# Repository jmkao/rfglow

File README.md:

rfglow
======

All the parts for an RF controlled RGB glow stick, in the style of a Ruifan KING BLADE (キングブレード http://ruifan.co.jp/pro_kb_x.html). In fact, making this work requires a diffuser from a KB since the diffuser itself cannot be 3D printed.

There are 3 basic component areas:
 * Electronics (Eagle files and BOM)
 * Microcontroller code (Arduino code)
 * Plastic handle (Inventor IPT files and STL files for 3D printing)

## Project Chat

## Status
This project is fairly usable, although could use some additional polish. All of the areas are sufficiently functional to demonstrate a proof of concept, but requires more testing before a device could actually be used in a physically demanding environment.

The primary items that need work are:
 * App for the BLE master
 * Handle design - Refactor to be more compact and with more practical design, especially for the coupler and attachemnt of the two halves
 * RF Master - Integrate a 0.96" color OLED screen, then design a PCB for it
 * RF Slave - Code something for the button to do

Then there are other interesting things that one could do with a microcontroller:
 * Fade commands
 * Color cycling commands
 * Slaves also act as command repeaters

Contributions welcome in all areas.

# Electronics
The PCB design is in the eagle folder and contains the schematic, PCB layout, and a set of gerber files (zipped together) for sending to a PCB fabrication service like Osh Park or Seeedstudio. (I had my first set made at Osh Park.)

The PCB is really a kind of motherboard for a variety of sub-assemblies (other boards sold as modules), principally:
 * RFBee from Seeedstudio
  * A Panstamp from panstamp.com can also be used as it has the same hardware (and is more compact, even). However, I don't have  board design to accomodate one (yet!)
 * Pololu S7V8A Adjustable Regulator (http://www.pololu.com/product/2118)
  * The potentiometer on this should be adjusted to output 3.7V before putting in place on the board
 * STP04CM05 LED Driver
  * The one I used for this design is a 14-DIP package not officially mentioned on the datasheet. I got mine from Digi-key (http://www.digikey.com/product-detail/en/STP04CM05B1R/497-6940-5-ND/1852497).
 * Vollong 3W RGB High Power Led and a matching lens
  * I got mine from http://www.superbrightleds.com/moreinfo/component-leds/vollong-3w-rgb-high-power-led/899/2214/
  * You'll need to bridge together the - leads into a common cathode configuration (the STP04CM05 is a sink driver)
 * Grove connectors from Seeedstudio cut up
  * I'm sure there's some spec for these, but I had a bunch of these lying around and used them for this purpose. Since you'll have to order an RFBee from them, you might as well get a bunch of cables from them (male on both sides so each cable can make two connectors) and PCB receptacles.
  * The color convention I'm using is:
    * Cable Red --> LED Red
    * Cable White --> LED Green
    * Cable Yellow --> LED Blue
    * Cable Black --> LED Common Ground
 * Adafruit nRF8001 (https://www.adafruit.com/products/1697)
  * Used for the rfglow_ble code which will relay commands from the nRF8001's BLE interface to the glow sticks.
  * Would allow a mobile app (e.g. iOS, Android) on a BLE capable device to control the glow sticks with a more advanced interface
  * A panstamp must be used as the microcontroller to build this device because the nRF8001 must be wired to the hardware SPI interface, and the RFBee does not expose the pins necessary to do this.

The version of the BLE master in this repository is for an unamplified version that uses a Panstamp. There is also an amplified designed that uses a CC1101+CC1190 evaluation module. The schematics and board layout for that were done in Upverter and are available at https://upverter.com/jkao/e86d81299623de9d/RFGlow-BLE-CC1109-Relay/

# Microcontroller Code

Arudino Code for 1.0.x.

 * rfglow_slave
  * Code for the glow sticks themselves
 * rfglow_master
  * Code for a potential master
  * Currently supported gestures:
   * Color change - short press on left and right
   * LED on/off - long press on the center to toggle
   * Auto color cycling mode - short press on center to toggle
   * Brightness change - long press on left or right
 * rfglow_ble
  * BLE based master that will relay color change commands over BLE to the RF glow sticks
  * Usable today for simple color changes with the iOS nRF UART or LightBlue apps
   * For nRF UART, send ASCII of 3 numbers separated by spaces, like "270 255 32\n". This is an HSV value, with the first digit as hue (0-359), second digit as saturation (0-255), and third digit as brightness (0-255)
   * For LightBlue (and really for any app you design yourself), send 4 bytes to the write characteristic of the service. The first 2 bytes are a 16-bit unsigned int for hue (only valid from 0-355), the 3rd byte is the unsigned 8-bit int for saturation, the 4th byte is the unsigned 8-bit int for brightness.
 * rfglow_serial
  * Code for when the master is connected to a computer, in which case you can enter the hue, saturation, and brightness as tuples over the serial line to send the command.
  * This code hasn't been touched in a while, and needs to have the radio settings from rfglow_master copied into it for it to actually work with the current version of rfglow_slave

The Arduino code depends on the following libraries:
 * ShiftPWM from https://github.com/elcojacobs/ShiftPWM
 * Panstamp for Arudino 1.0.x, currently panstamp_library.zip from http://www.panstamp.com/downloads
  * Uses only the CC1101 libraries and not the SWAP stack
 * ClickButton from https://code.google.com/p/clickbutton/downloads/list
  * Only needed by rfglow_master currently for the button behavior

# Plastic Handle

Autodesk Inventor parts and assembly with the current design, to be FFF 3D printed (e.g. <45 degree overhangs, etc...).

This design is quite messy becuase my CAD skills are weak, and the parameters are difficult to adjust. However, it is functional with the following features:
* Lip-and-groove attachment between top and bottom halves to facilitate alignment
 * There is some clearance, so the groove is deeper than the lip sticks out
* Coupler to screw on a king blade diffuser on one end, then attach to the handle
* Cups for magnets to help hold the top and bottom together (0.25" X 0.125" X 0.0625" rare earth)

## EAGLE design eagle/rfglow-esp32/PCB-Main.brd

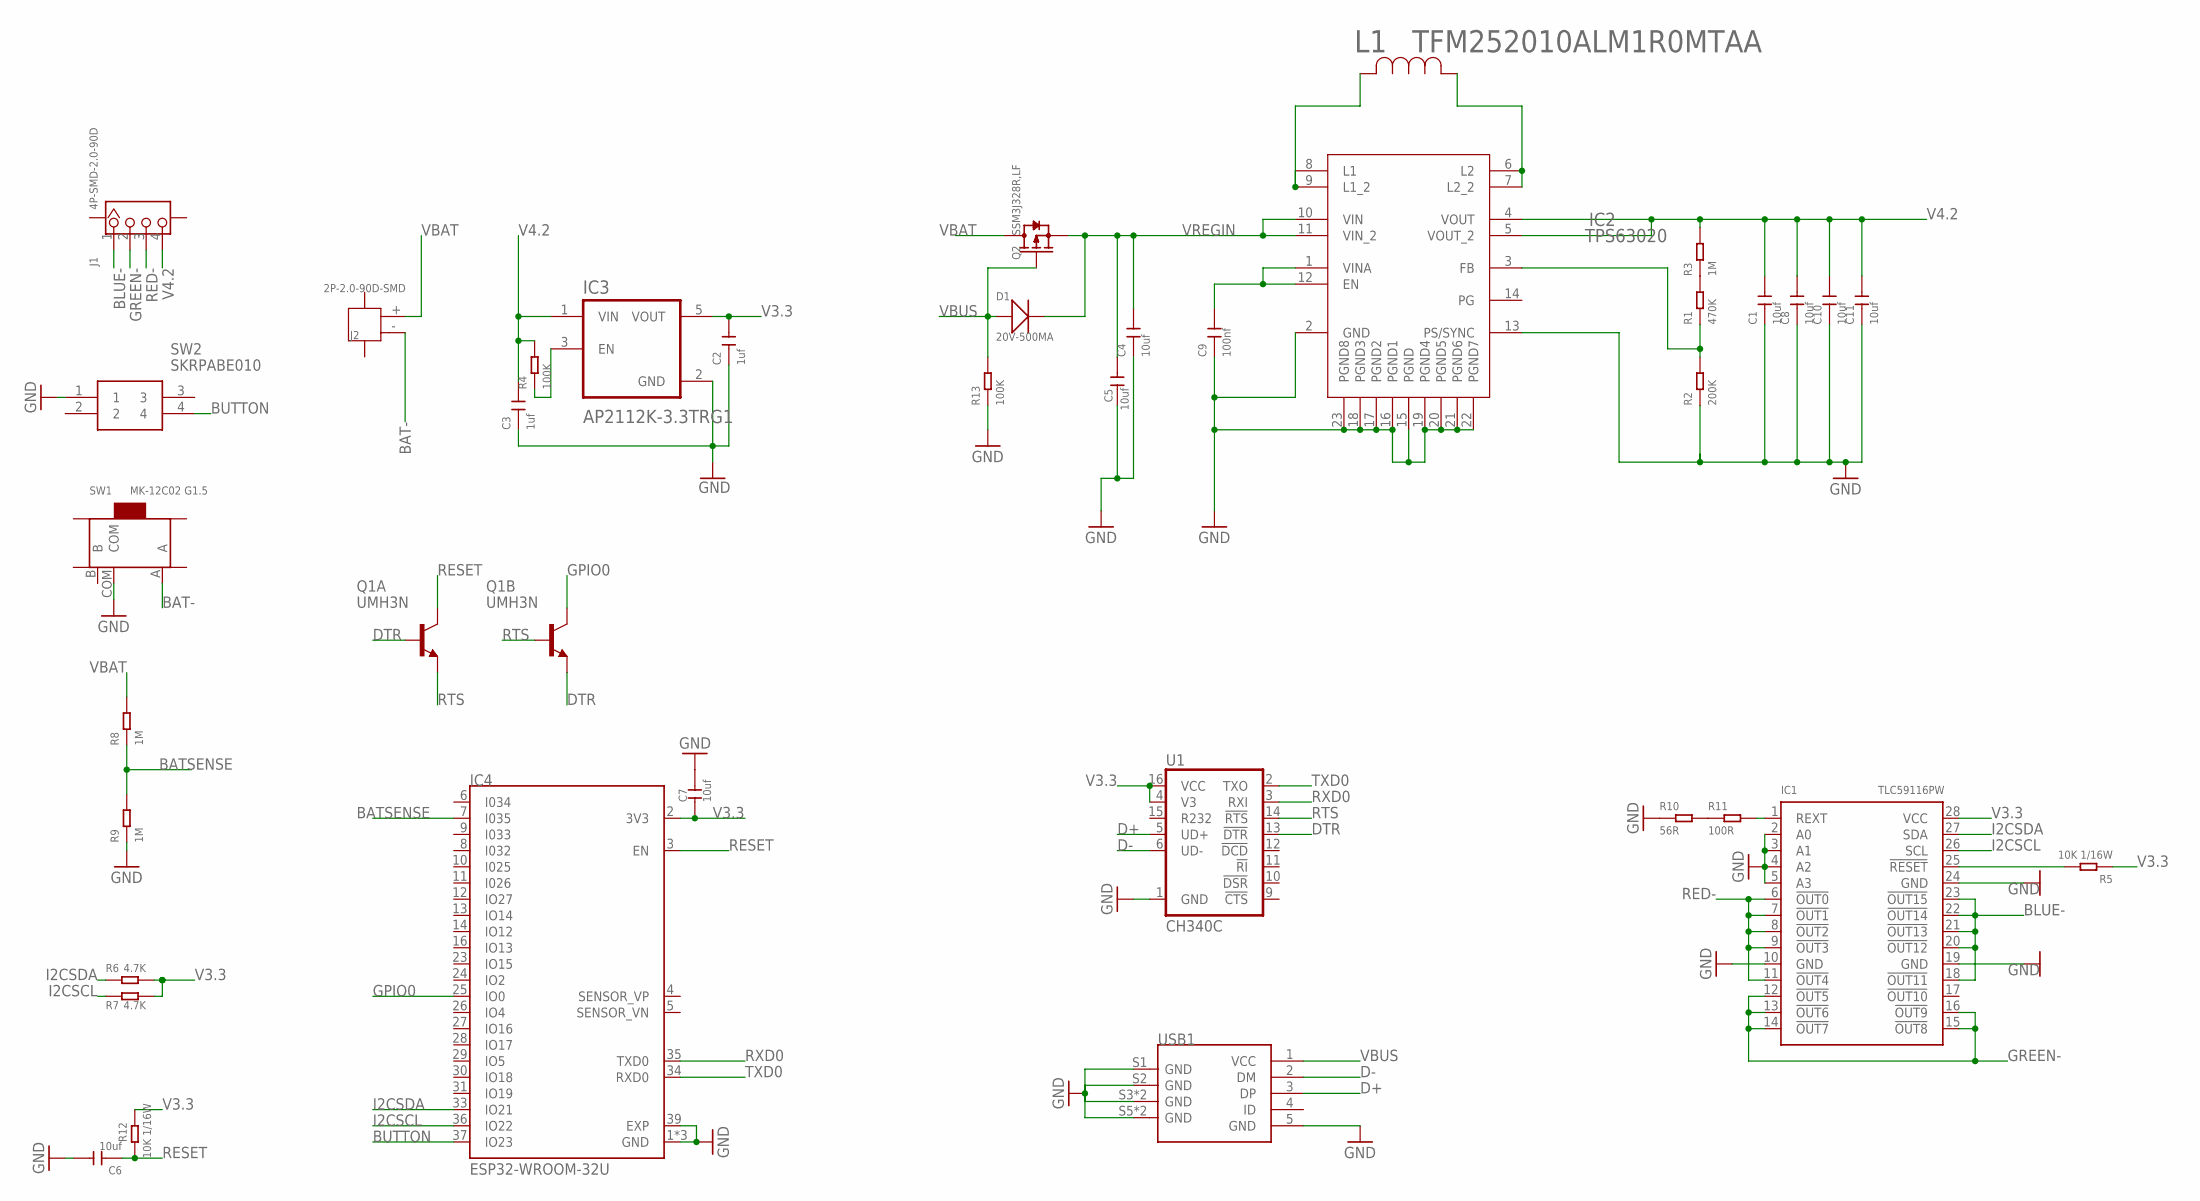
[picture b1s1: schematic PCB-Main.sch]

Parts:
C1, C4, C5, C6, C7, C8, C10, C11: 10uf; C0402
C2, C3: 1uf; C0402
C9: 100nf; C0402
D1: 20V-500MA; SOD-123
IC1: TLC59116PW; PW_R-PDSO-G28
IC2: TPS63020; QFN14-3X4MM
IC3: AP2112K-3.3TRG1; SOT95P285X140-5N
IC4: ESP32-WROOM-32U; XCVR_ESP32-WROOM-32U
J1: 4P-SMD-2.0-90D; HW4-SMD-2.0-90D
J2: 2P-2.0-90D-SMD; HW2-SMD-2.0-90D
L1: TFM252010ALM1R0MTAA; IND_1008
Q1: UMH3N; UMT6
Q2: SSM3J328R,LF; SOT-23
R1: 470K; R0402
R2: 200K; R0402
R3, R8, R9: 1M; R0402
R4, R13: 100K; R0402
R5, R12: 10K 1/16W; R0402
R6, R7: 4.7K; R0402
R10: 56R; R0402
R11: 100R; R0402
SW1: MK-12C02 G1.5; SW7-SMD-L6.7X2.7X3.2MM
SW2: SKRPABE010; SMT(4.2X3.2)
U1: CH340C; SO016
USB1: 10118193-0001LF; MICRO-USB5+6P-SMD-0.65-B

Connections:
BAT-: J2.- (2), SW1.A
BATSENSE: IC4.7 (I035), R8.1, R9.2
BLUE-: IC1.18 (!OUT11), IC1.20 (!OUT12), IC1.21 (!OUT13), IC1.22 (!OUT14), IC1.23 (!OUT15), J1.1
BUTTON: IC4.37 (IO23), SW2.4
D+: U1.5 (UD+), USB1.3 (DP)
D-: U1.6 (UD-), USB1.2 (DM)
DTR: Q1.2 (B), Q1.4 (E), U1.13 (!DTR)
GND: C1.1, C2.1, C3.1, C4.1, C5.1, C6.2, C7.2, C8.1, C9.1, C10.1, C11.1, IC1.2 (A0), IC1.3 (A1), IC1.4 (A2), IC1.5 (A3), IC1.10 (GND), IC1.19 (GND), IC1.24 (GND), IC2.2 (GND), IC2.13 (PS/SYNC), IC2.15 (PGND), IC2.16 (PGND1), IC2.17 (PGND2), IC2.18 (PGND3), IC2.19 (PGND4), IC2.20 (PGND5), IC2.21 (PGND6), IC2.22 (PGND7), IC2.23 (PGND8), IC3.2 (GND), IC4.1 (GND), IC4.15 (GND), IC4.38 (GND), IC4.39 (EXP), R2.1, R9.1, R10.1, R13.1, SW1.COM, SW2.1, U1.1 (GND), USB1.5 (GND), USB1.S1 (GND), USB1.S2 (GND), USB1.S3 (GND), USB1.S4 (GND), USB1.S5 (GND), USB1.S6 (GND)
GPIO0: IC4.25 (IO0), Q1.3 (C)
GREEN-: IC1.12 (!OUT5), IC1.13 (!OUT6), IC1.14 (!OUT7), IC1.15 (!OUT8), IC1.16 (!OUT9), J1.2
I2CSCL: IC1.26 (SCL), IC4.36 (IO22), R7.1
I2CSDA: IC1.27 (SDA), IC4.33 (IO21), R6.1
unnamed: C9.2, IC2.1 (VINA), IC2.12 (EN)
unnamed: IC1.1 (REXT), R11.2
unnamed: R1.2, R3.1
unnamed: IC3.3 (EN), R4.1
unnamed: R10.2, R11.1
unnamed: IC2.8 (L1), IC2.9 (L1_2), L1.2
unnamed: IC1.25 (!RESET), R5.2
unnamed: IC2.6 (L2), IC2.7 (L2_2), L1.1
unnamed: IC2.3 (FB), R1.1, R2.2
RED-: IC1.6 (!OUT0), IC1.7 (!OUT1), IC1.8 (!OUT2), IC1.9 (!OUT3), IC1.11 (!OUT4), J1.3
RESET: C6.1, IC4.3 (EN), Q1.6 (C), R12.1
RTS: Q1.1 (E), Q1.5 (B), U1.14 (!RTS)
RXD0: IC4.35 (TXD0), U1.3 (RXI)
TXD0: IC4.34 (RXD0), U1.2 (TXO)
V3.3: C2.2, C7.1, IC1.28 (VCC), IC3.5 (VOUT), IC4.2 (3V3), R5.1, R6.2, R7.2, R12.2, U1.4 (V3), U1.16 (VCC)
V4.2: C1.2, C3.2, C8.2, C10.2, C11.2, IC2.4 (VOUT), IC2.5 (VOUT_2), IC3.1 (VIN), J1.4, R3.2, R4.2
VBAT: J2.+ (1), Q2.3 (D), R8.2
VBUS: D1.+, Q2.1 (G), R13.2, USB1.1 (VCC)
VREGIN: C4.2, C5.2, D1.-, IC2.10 (VIN), IC2.11 (VIN_2), Q2.2 (S)

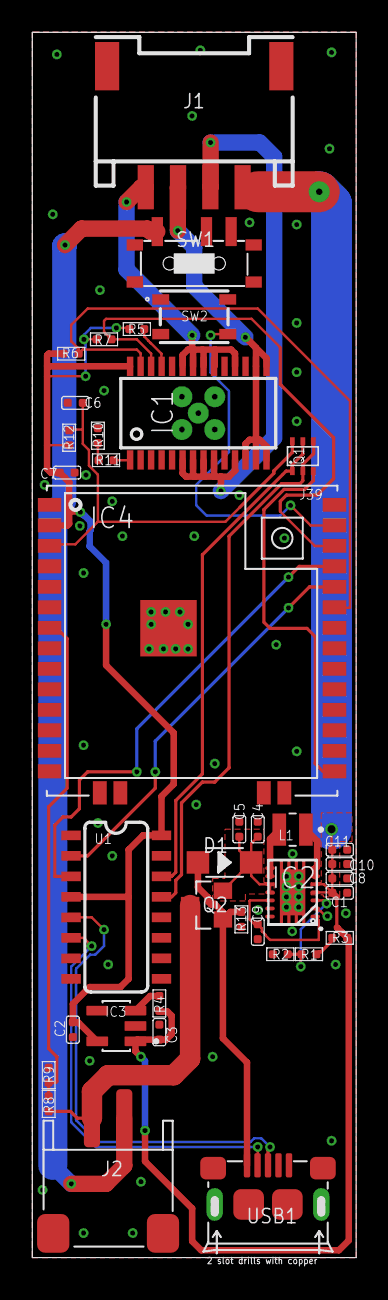
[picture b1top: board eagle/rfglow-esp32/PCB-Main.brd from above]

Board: 2 copper layers, 20.1 x 75.9 mm, 38 parts (0 on the bottom side), 31 nets.

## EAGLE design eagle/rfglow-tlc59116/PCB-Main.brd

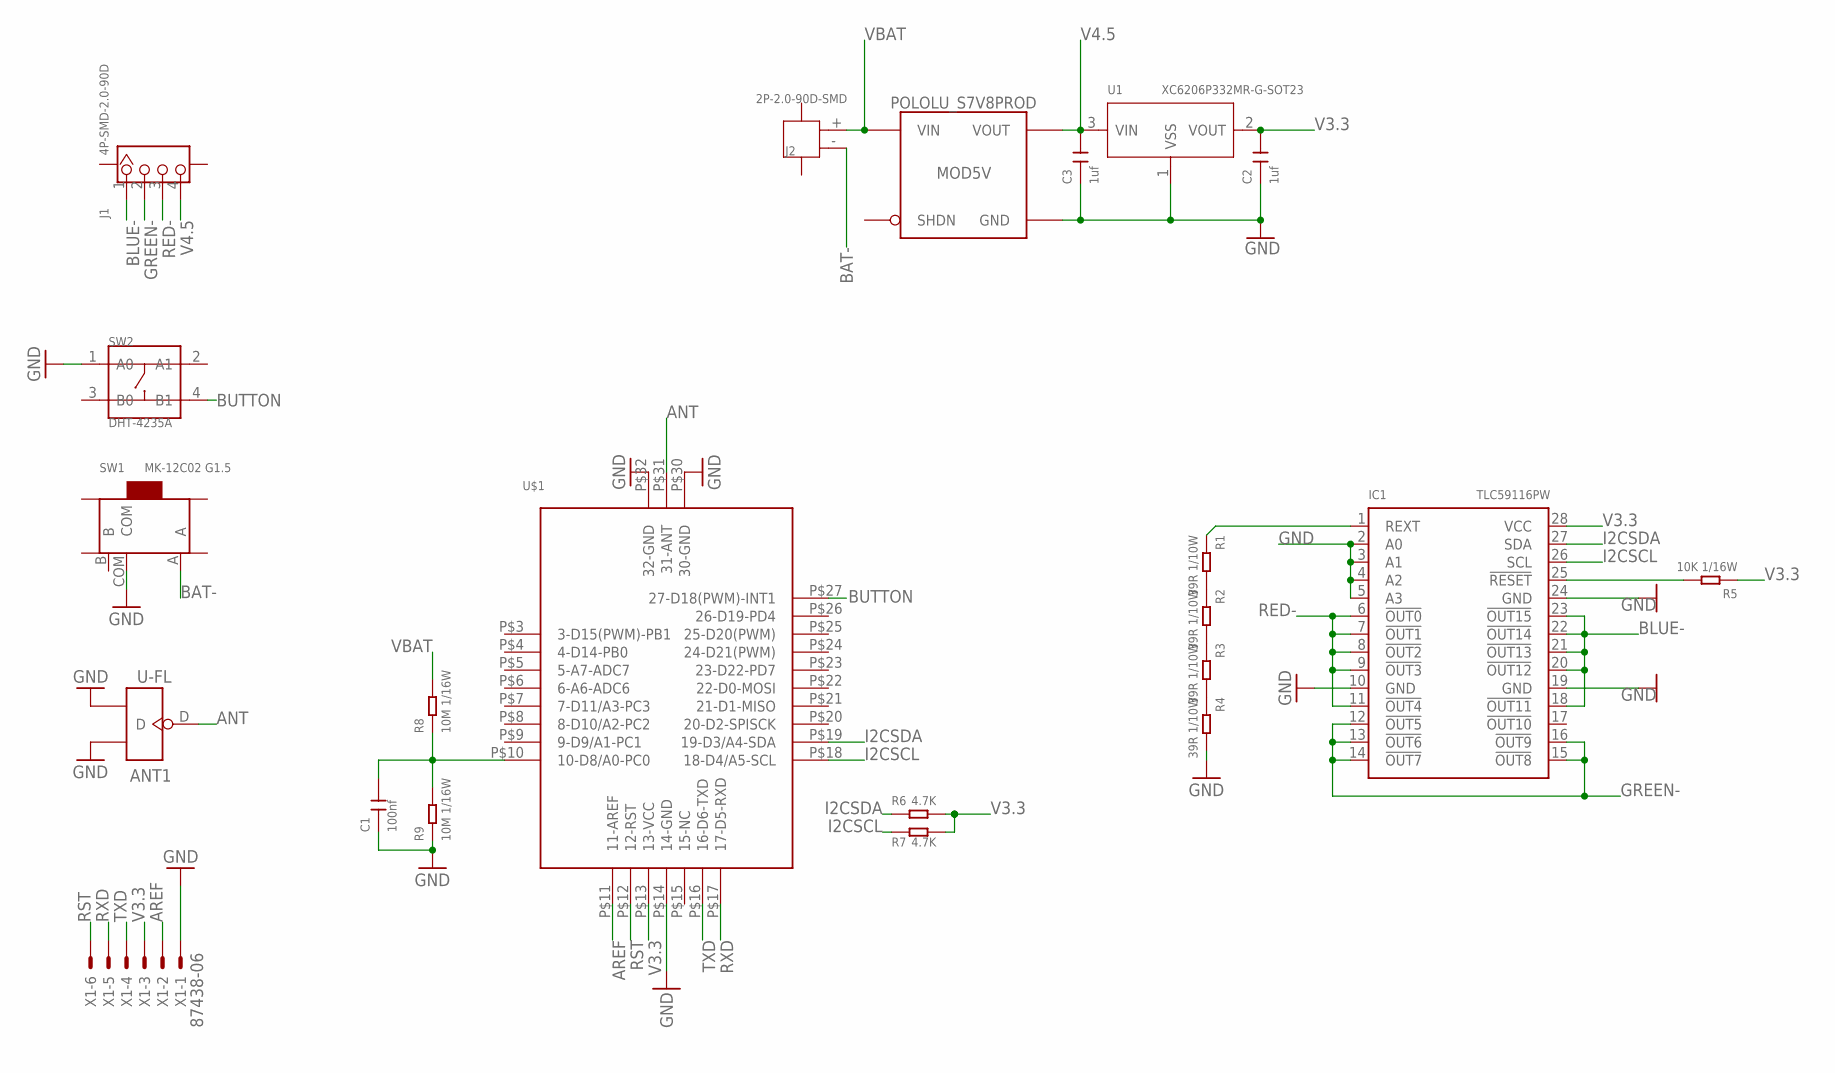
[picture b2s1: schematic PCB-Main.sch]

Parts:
ANT1: U-FL; U-FL3P-SMD-2.6X2.6X1.0MM
C1: 100nf; C0402
C2, C3: 1uf; C0402
IC1: TLC59116PW; PW_R-PDSO-G28
J1: 4P-SMD-2.0-90D; HW4-SMD-2.0-90D
J2: 2P-2.0-90D-SMD; HW2-SMD-2.0-90D
MOD5V: POLOLU_S7V8PROD; POLOLU_4P_SIGO
R1, R2, R3, R4: 39R 1/10W; R0603
R5: 10K 1/16W; R0402
R6, R7: 4.7K; R0402
R8, R9: 10M 1/16W; R0402
SW1: MK-12C02 G1.5; SW7-SMD-L6.7X2.7X3.2MM
SW2: DHT-4235A; SW4-SMD-4.2X3.2X2.5MM
U1: XC6206P332MR-G-SOT23; SOT-23
U$1: PANSTAMP-AVR-2; SMD-PAD-34
X1: 87438-06

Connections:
ANT: ANT1.D, U$1.P$31 (31-ANT)
AREF: U$1.P$11 (11-AREF), X1.2
BAT-: J2.- (2), SW1.A
BLUE-: IC1.18 (!OUT11), IC1.20 (!OUT12), IC1.21 (!OUT13), IC1.22 (!OUT14), IC1.23 (!OUT15), J1.1
BUTTON: SW2.4 (B1), U$1.P$27 (27-D18(PWM)-INT1)
GND: ANT1.GND1, ANT1.GND2, C1.1, C2.1, C3.1, IC1.2 (A0), IC1.3 (A1), IC1.4 (A2), IC1.5 (A3), IC1.10 (GND), IC1.19 (GND), IC1.24 (GND), MOD5V.G (GND), R4.2, R9.1, SW1.COM, SW2.1 (A0), U1.1 (VSS), U$1.P$14 (14-GND), U$1.P$30 (30-GND), U$1.P$32 (32-GND), X1.1
GREEN-: IC1.12 (!OUT5), IC1.13 (!OUT6), IC1.14 (!OUT7), IC1.15 (!OUT8), IC1.16 (!OUT9), J1.2
I2CSCL: IC1.26 (SCL), R7.1, U$1.P$18 (18-D4/A5-SCL)
I2CSDA: IC1.27 (SDA), R6.1, U$1.P$19 (19-D3/A4-SDA)
unnamed: R1.2, R2.1
unnamed: R2.2, R3.1
unnamed: R3.2, R4.1
unnamed: IC1.25 (!RESET), R5.2
unnamed: IC1.1 (REXT), R1.1
unnamed: C1.2, R8.1, R9.2, U$1.P$10 (10-D8/A0-PC0)
RED-: IC1.6 (!OUT0), IC1.7 (!OUT1), IC1.8 (!OUT2), IC1.9 (!OUT3), IC1.11 (!OUT4), J1.3
RST: U$1.P$12 (12-RST), X1.6
RXD: U$1.P$17 (17-D5-RXD), X1.5
TXD: U$1.P$16 (16-D6-TXD), X1.4
V3.3: C2.2, IC1.28 (VCC), R5.1, R6.2, R7.2, U1.2 (VOUT), U$1.P$13 (13-VCC), X1.3
V4.5: C3.2, J1.4, MOD5V.O (VOUT), U1.3 (VIN)
VBAT: J2.+ (1), MOD5V.I (VIN), R8.2

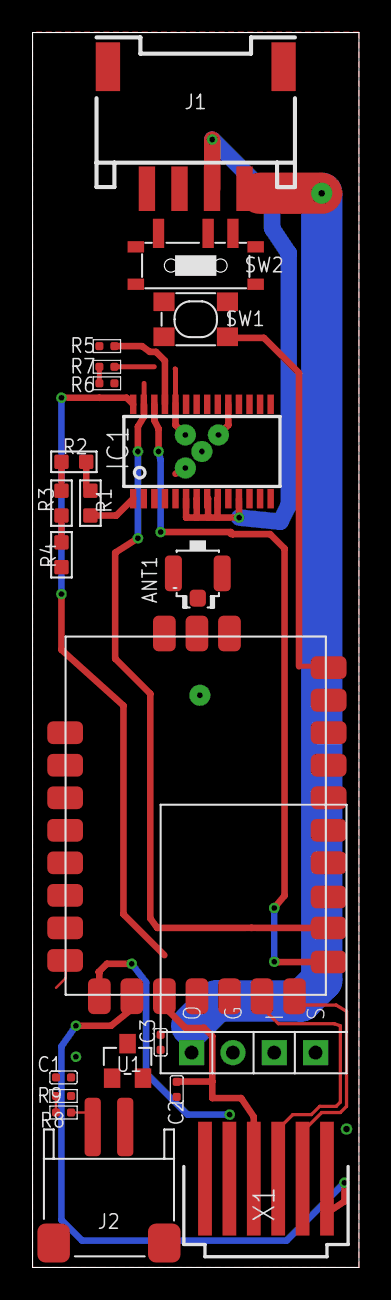
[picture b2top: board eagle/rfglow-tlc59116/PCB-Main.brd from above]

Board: 2 copper layers, 20.1 x 75.9 mm, 22 parts (0 on the bottom side), 22 nets.

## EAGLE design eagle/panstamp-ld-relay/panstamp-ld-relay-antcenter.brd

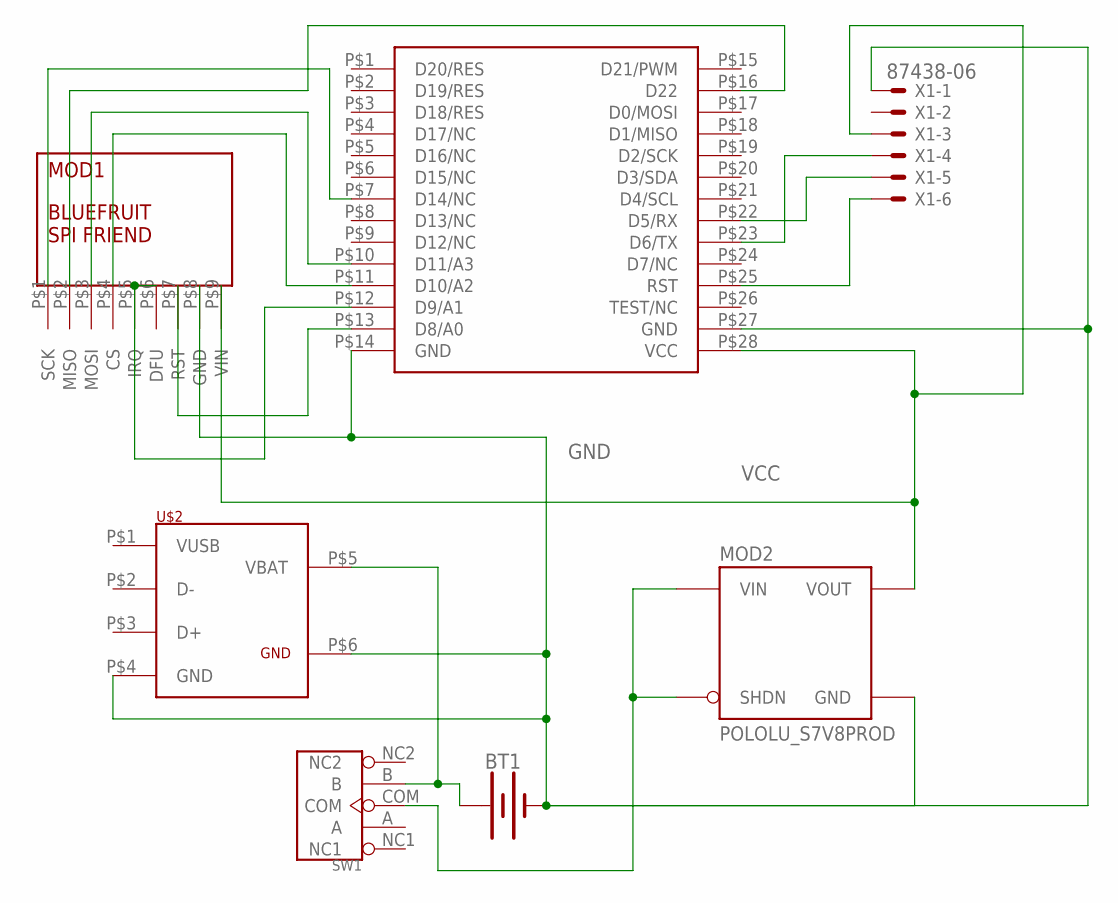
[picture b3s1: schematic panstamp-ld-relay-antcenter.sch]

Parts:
BT1: BATTERY-18650; BATTERY_18650-HOLDER
MOD1: BLUEFRUIT-SPI
MOD2: POLOLU_S7V8PROD; POLOLU_4P_SIGO
SW1: DIP-TOGGLE-SWITCH-ON-ON(3+2P-8.8X4.6MM)-90D; SW5-2.0-8.8X4.4X4.7MM-90D
U$1: PANSTAMP-LD
U$2: JS-1965
X1: 87438-06

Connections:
GND: BT1.GND@1 (-), MOD1.P$8 (GND), MOD2.G (GND), U$1.P$14 (GND), U$1.P$27 (GND), U$2.P$4 (GND), U$2.P$6 (GND), X1.1
unnamed: U$1.P$23 (D6/TX), X1.4
unnamed: MOD1.P$2 (MISO), U$1.P$16 (D22)
unnamed: MOD1.P$4 (CS), U$1.P$11 (D10/A2)
unnamed: MOD1.P$3 (MOSI), U$1.P$10 (D11/A3)
unnamed: MOD1.P$7 (RST), U$1.P$13 (D8/A0)
unnamed: MOD1.P$1 (SCK), U$1.P$7 (D14/NC)
unnamed: MOD2.I (VIN), MOD2.S (SHDN), SW1.COM
unnamed: MOD1.P$5 (IRQ), U$1.P$12 (D9/A1)
unnamed: U$1.P$22 (D5/RX), X1.5
unnamed: U$1.P$25 (RST), X1.6
VBAT: BT1.PWR@1 (+), SW1.B, U$2.P$5 (VBAT)
VCC: MOD1.P$9 (VIN), MOD2.O (VOUT), U$1.P$28 (VCC), X1.3

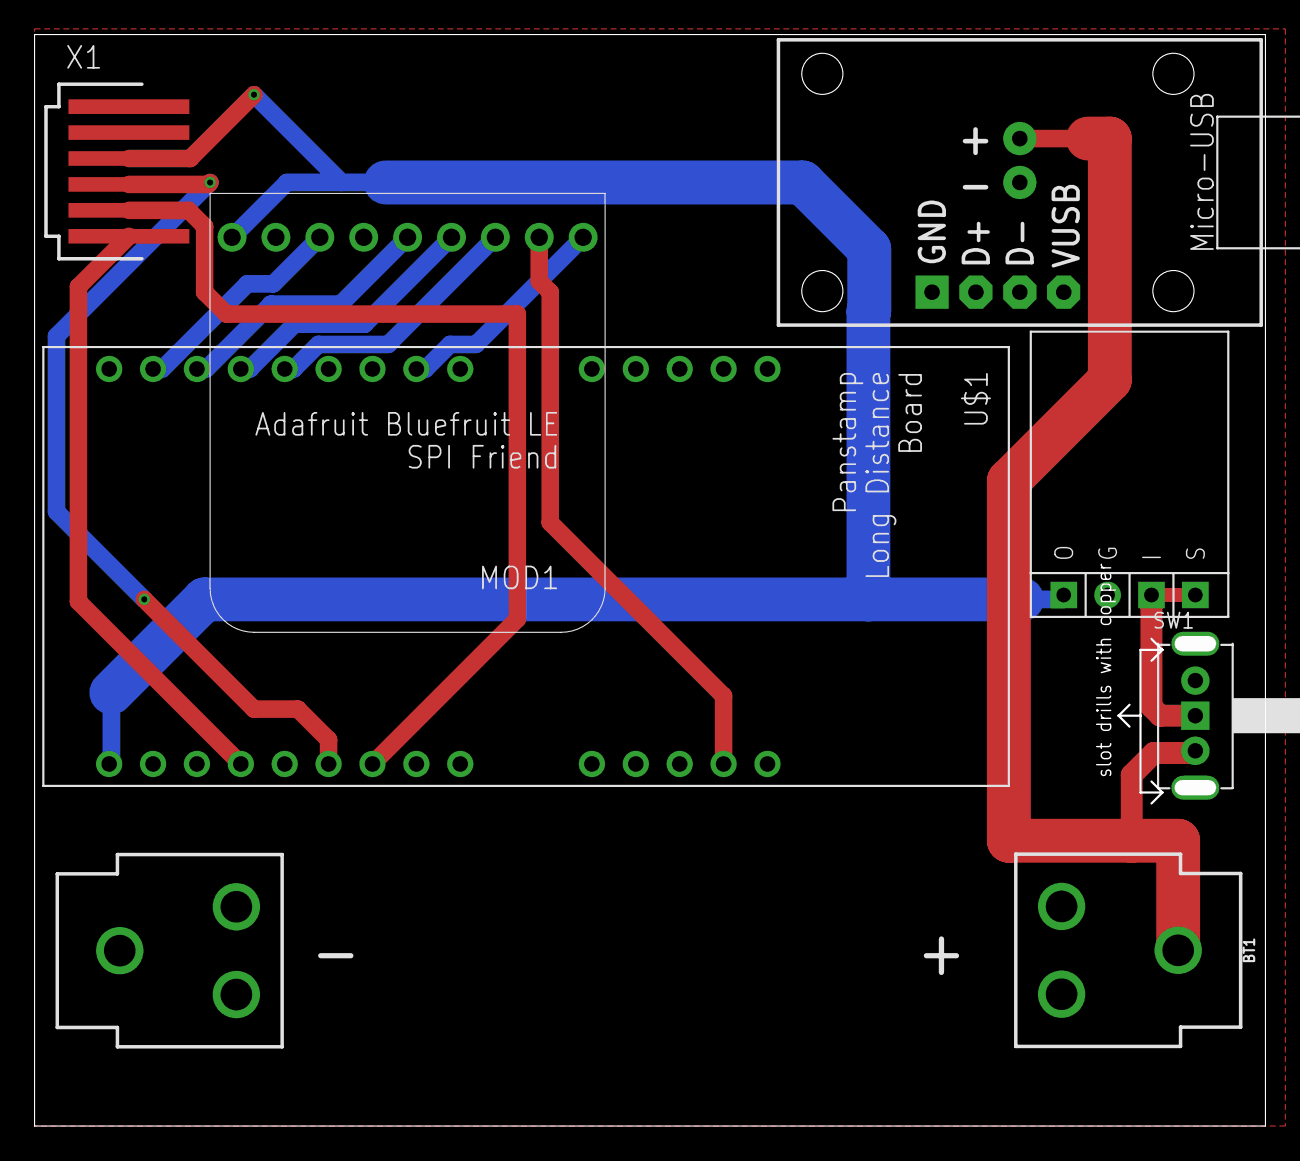
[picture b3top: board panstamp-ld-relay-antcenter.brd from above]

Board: 2 copper layers, 71.2 x 63.2 mm, 7 parts (0 on the bottom side), 13 nets.

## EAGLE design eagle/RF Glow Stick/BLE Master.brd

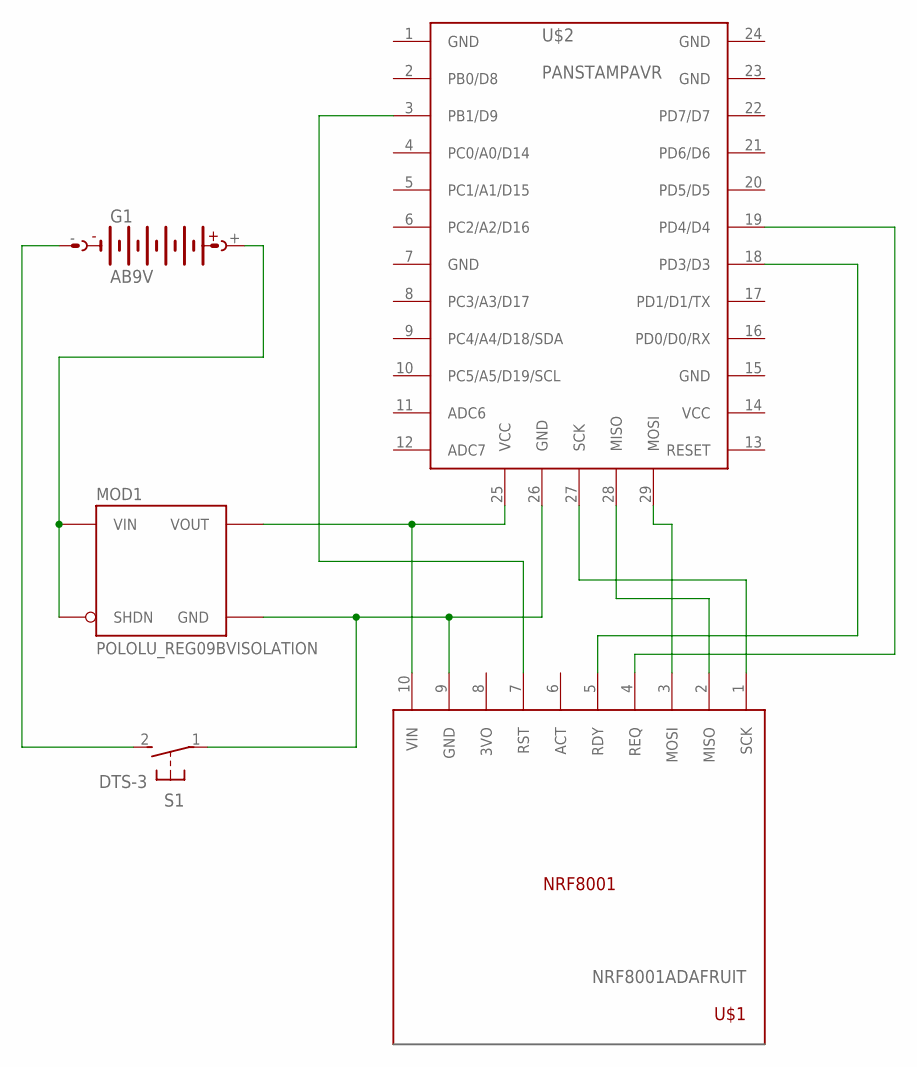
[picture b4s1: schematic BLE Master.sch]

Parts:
G1: AB9V
MOD1: POLOLU_REG09BVISOLATION; POLOLU_REG09B_ISO
S1: DTS-3
U$1: NRF8001ADAFRUIT; NRF8001_ADAFRUIT
U$2: PANSTAMPAVR; PANSTAMP

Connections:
unnamed: G1.+, MOD1.I (VIN), MOD1.S (SHDN)
unnamed: G1.-, S1.2
unnamed: MOD1.G (GND), S1.1, U$1.9 (GND), U$2.26 (GND)
unnamed: U$1.1 (SCK), U$2.27 (SCK)
unnamed: U$1.2 (MISO), U$2.28 (MISO)
unnamed: U$1.3 (MOSI), U$2.29 (MOSI)
unnamed: U$1.4 (REQ), U$2.19 (PD4/D4)
unnamed: U$1.5 (RDY), U$2.18 (PD3/D3)
unnamed: U$1.7 (RST), U$2.3 (PB1/D9)
unnamed: MOD1.O (VOUT), U$1.10 (VIN), U$2.25 (VCC)

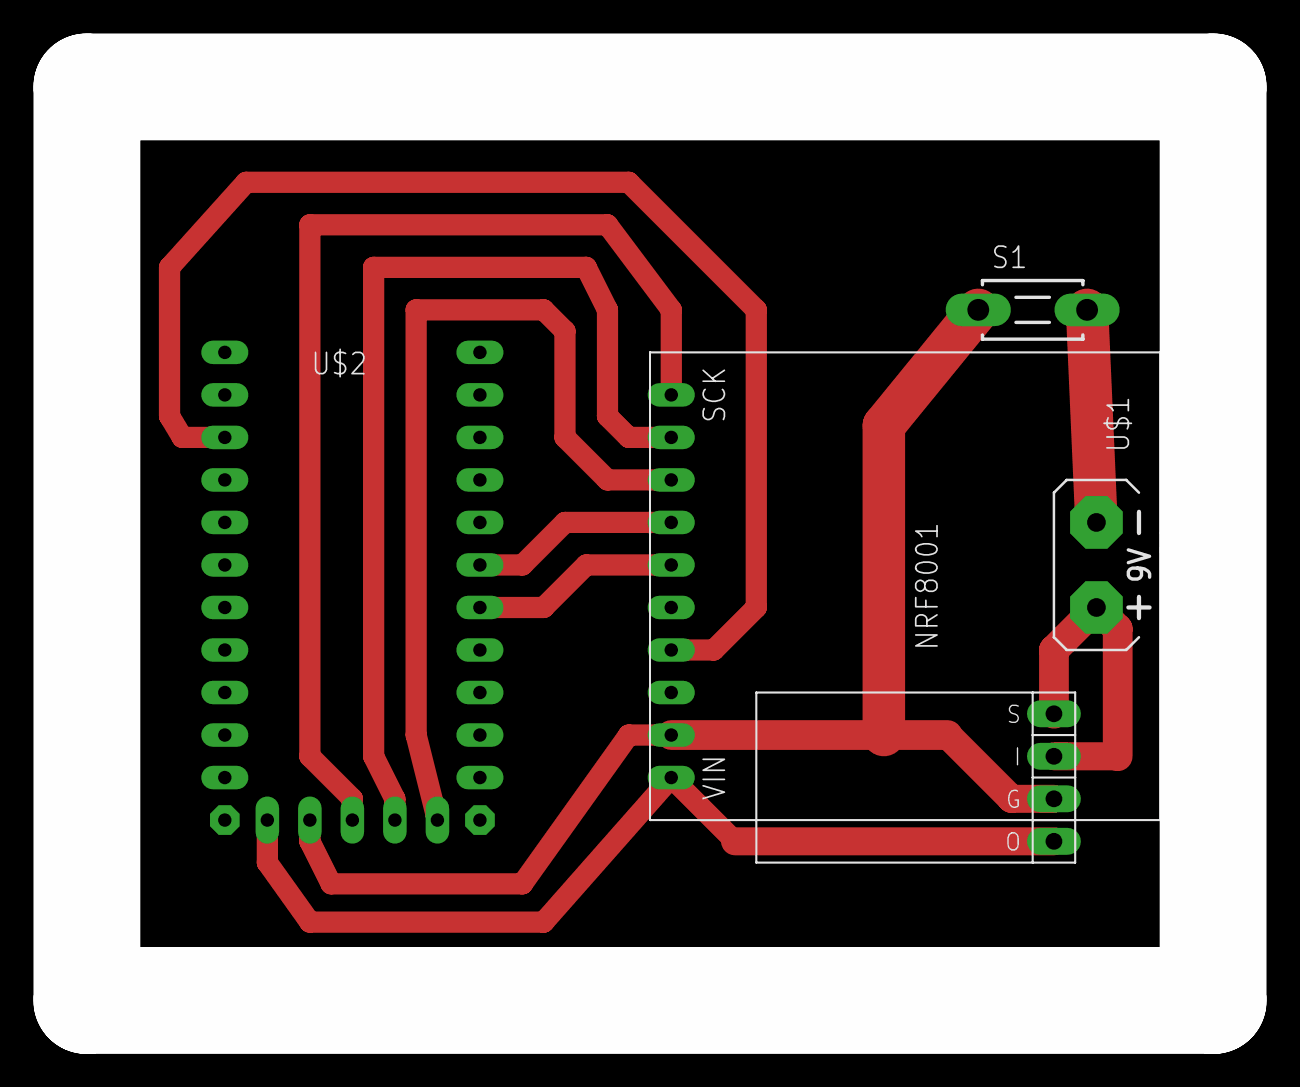
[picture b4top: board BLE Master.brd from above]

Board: 2 copper layers, 67.3 x 54.6 mm, 5 parts (0 on the bottom side), 10 nets.

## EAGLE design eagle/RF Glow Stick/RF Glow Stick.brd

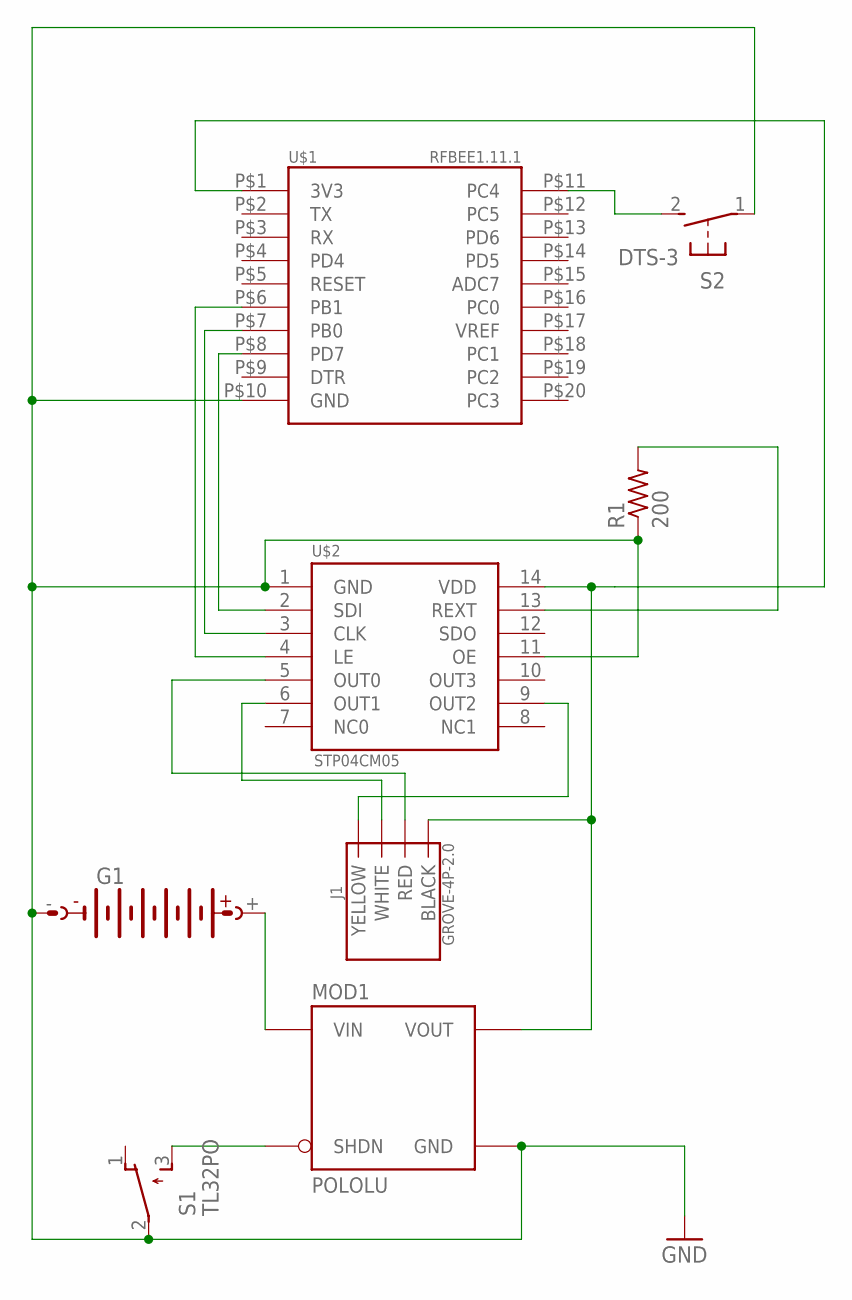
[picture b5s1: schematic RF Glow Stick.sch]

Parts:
G1: AB9V
J1: GROVE-4P-2.0; 4P-2.0-90D
MOD1: POLOLU; POLOLU_REG09B
R1: 200; 0309/12
S1: TL32PO; TL3XPO
S2: DTS-3
U$1: RFBEE1.11.1; RFBEE
U$2: STP04CM05; DIL14

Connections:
BATT: G1.+, MOD1.I (VIN)
GND: G1.-, MOD1.G (GND), R1.1, S1.2, S2.1, U$1.P$10 (GND), U$2.1 (GND), U$2.11 (OE)
unnamed: J1.RED, U$2.5 (OUT0)
unnamed: MOD1.S (SHDN), S1.3 (S)
unnamed: S2.2, U$1.P$11 (PC4)
unnamed: U$1.P$6 (PB1), U$2.4 (LE)
unnamed: U$1.P$7 (PB0), U$2.3 (CLK)
unnamed: U$1.P$8 (PD7), U$2.2 (SDI)
unnamed: J1.WHITE, U$2.6 (OUT1)
unnamed: J1.YELLOW, U$2.9 (OUT2)
unnamed: R1.2, U$2.13 (REXT)
VOUT: J1.BLACK, MOD1.O (VOUT), U$1.P$1 (3V3), U$2.14 (VDD)

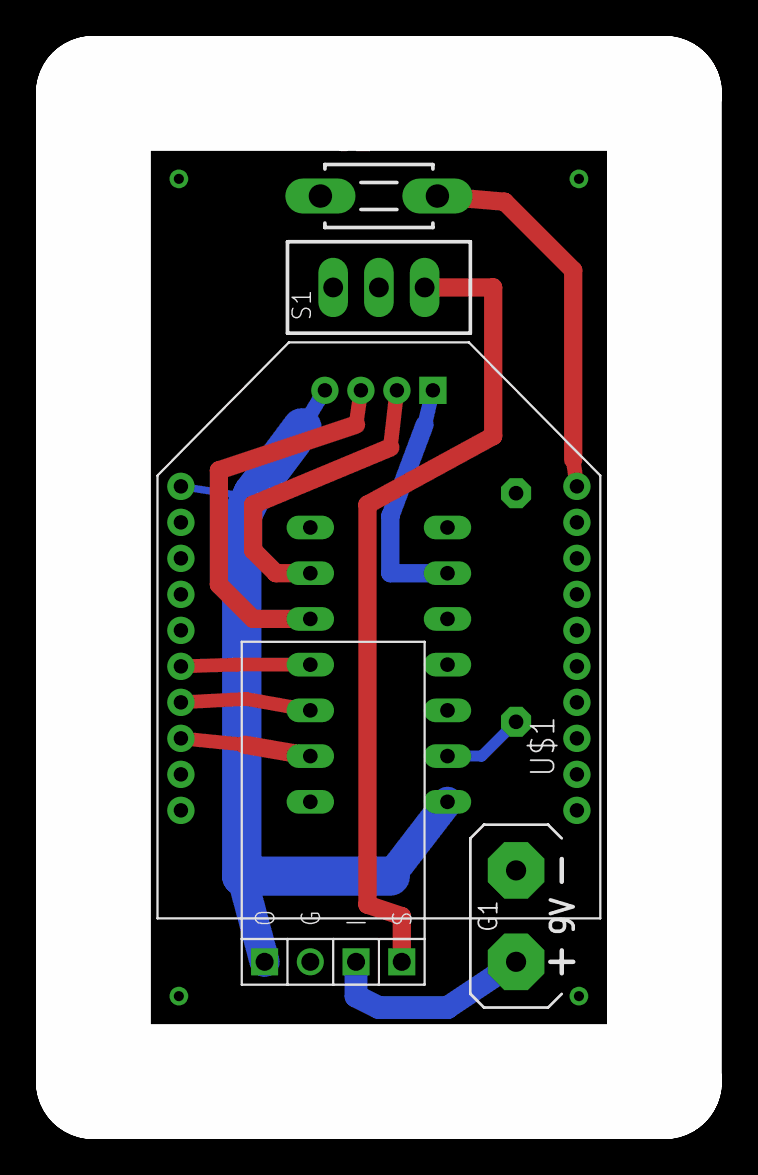
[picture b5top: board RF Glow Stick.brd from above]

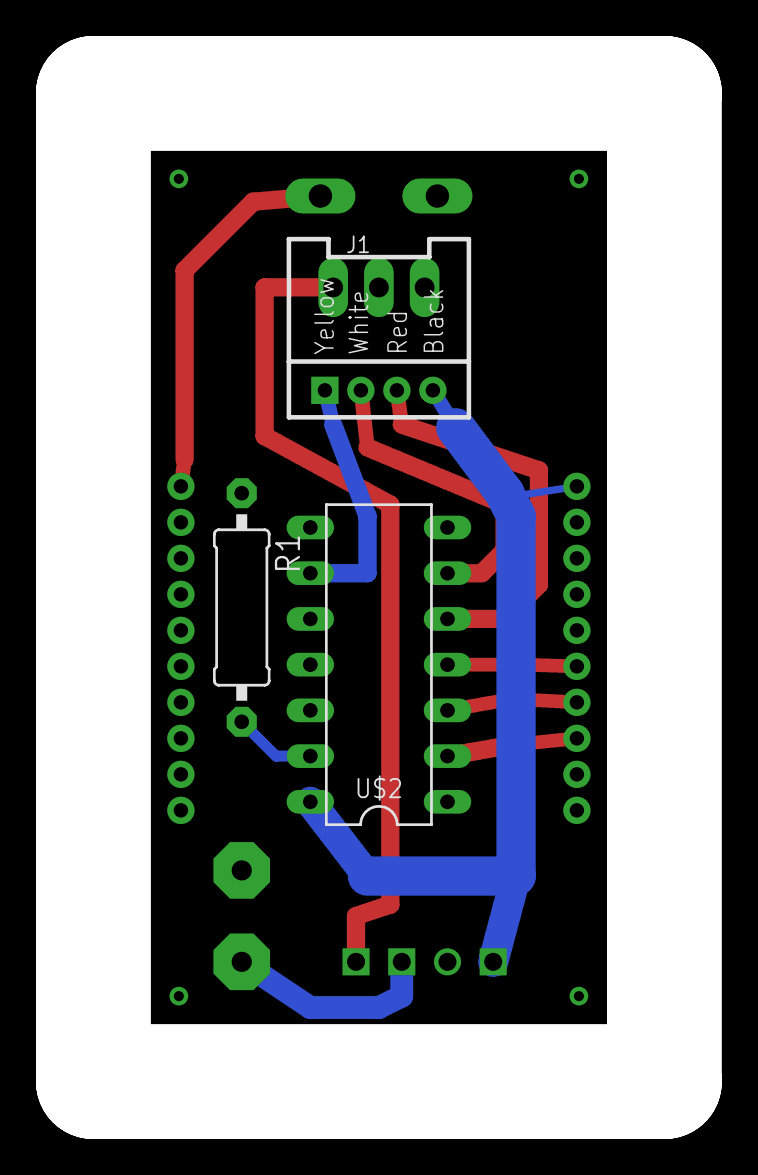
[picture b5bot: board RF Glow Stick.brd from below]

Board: 2 copper layers, 31.8 x 54.9 mm, 8 parts (3 on the bottom side), 12 nets.

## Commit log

2014-09-08 Updated slave to PWM at 1200Hz Master now has on/off controls via long-press
2014-09-08 Reorganized output gerbers Updated schemate to move power switch to front end and a tactile switch to PC4 (Arduino pin 18)
2014-09-08 Reorganized eagle files Added fillets to handles and include printable STL files
2014-09-08 Added long press left/right to change brightness level
2014-09-13 Disable adc to save an undetectable amount of power. Real power draw is from the CC1101
2014-09-13 Updated design to prevent holes in the shell due to fillets, shore up the wobbly coupler, and split the top into a battery and main portion
2014-09-14 cleaned up commented out part from rfglow_serial
2014-10-05 Fixed flawed board design. The LED connector needs to be in the middle to clear the PCB holding ledges and to have maximum clearance for round handles. Also reduced the side of the board from 5.08cm 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
2014-10-05 Added cutouts to the handle top to access the switches in the v2 pcb design. Thickened many handle walls to 1.5mm
2014-10-26 Added magnet pockets and verified cutout for switches is functional.
    Cutout in coupler for alignment tabs is not quite right, still reqires filing for the bottom
2014-10-26 Updated board to be compatible with milling fabrication (e.g. a CNC mill with an engraving tool for isolation routing). However, actual isolution routed board is nonfunctional because the design reli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
2014-10-26 Added serial output when commands are received for easier debugging of newly flashed boards.
2014-10-31 Changed protocol to reduce fixed packet length from 0x10 to 0x5 bytes. Added a BLE master which relays messages from a BLE Central device to the glow sticks to enable app-based control. (Using Adafru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
2014-10-31 Added dependant Arduino libraries as submodules (for those which are in github) or copies (for those which are not)
2014-10-31 Added additional clearance to lip and widened battery lead clearance holes
2014-10-31 Added isolation milling gcode for shopbot Mainly as an example, since isolation milled boards are nonfunctional unless the through holes are plated somehow
2014-10-31 Added .gitmodules for github based arduino library submodules
2014-11-01 Document recent changes that take the system to moderately functional use.
2014-11-04 Added BLE master eagle files
2014-11-04 Added Arduino code for the BLE master
2015-10-31 Fixed typo
2015-11-03 Add mobile app code
2015-11-06 Reduced size of package for faster iPhone 4S download
2015-11-26 Updated slave to make use of the button
2017-06-29 Catchup update, sorry...
2017-07-14 Update for multi-card swipe buttons and telemetry
2017-07-16 Adding new code for using the TI TCL59116 LED driver
2017-07-25 Added new slave board for tlc59116
2017-07-28 Adding new Ionic 2 project
2017-08-17 CLeaned up gerbers, fixed serious circuit errors
2017-08-20 Updates to board
2017-08-21 Beginning work on ionic 2
2017-08-21 Removed unnecesary 3rd party files, keep those separate
2017-08-21 Update code to OneButton, and switch to use library-controlled arduino-TCL59116.
2017-08-26 Updated Arduino code for Panstamp SDK 1.5.7 and Arduino IDE 1.8.3, using boards. Radio configuration is now done in the board library in cc1101.h instead of in this code.
2017-08-26 Eagle version update in project
2017-09-11 Reset ionic project
2017-09-11 Init new ionic project
2017-09-11 Updated for local project
2017-10-30 Added code for the BLE controller implemented with a PanStamp long distance board and the Adafruit Bluefruit LE SPI Friend
2017-11-01 Restart with new ionicjs.com
2017-11-13 Decreased min refresh interval for BLE controller, removed unused ionic remnants
2017-11-13 Added some models for tlc59116 accessories
2017-11-20 Added untested code for controlling current
2017-11-23 Changed HSV-RGB conversion to be constant brightness
2017-12-05 Fixes based on field test
2017-12-27 Component setup for Panstamp LD to BLE relay board
2018-04-13 Adding components to build PCB for relay
2018-05-05 Real PCB for relay board, update handle to reduce submodules and use a u.FL antenna connector.
2018-05-07 Adding Wear OS controller
2018-05-08 Fixup some Intellij artifacts
2018-05-18 Added smartrf configurations
2018-05-20 Added nodejs tools to import and export cloud firestore
2018-05-20 Some android changes
2018-05-20 Fixup some radio config conflicts
2018-05-21 Cloud Firestore based button config complete
2018-05-21 Update gradle config for Nordic BLE library, min SDK 26 now.
2018-05-21 Fix missing dependency
2018-05-22 Idea config changes
2018-05-23 Add Gitter badge
2018-05-23 Add a Gitter chat badge to README.md (#1)
    * Add Gitter badge
    * Update README.md
2018-05-28 BLE communication is working
2018-06-01 Added initial FHSS impelemtnation
2018-06-16 Get ready for the rest of the menus
2018-06-16 Initial string resoure loading
2018-06-25 Menu system functional, FHSS functional. Working on relay box fades
2018-06-27 Relay controlled fading works. Pass 6 bytes instead of 4 over BLE, and the last 2 bytes will be interpreted as an unsigned int for the ms to transition from current color to the payload defined color.
2018-06-27 A few fixes to handle maLevel properly
2018-07-01 Added send fade
2018-07-02 Menu updates
2018-07-03 Removed firestore from core repo
2018-07-03 Fix button lockout interaction with FHSS
2018-07-03 Fading
2018-07-03 Add panstamp modifications
2018-07-04 Final fixes
2018-11-27 Updated button pin for newest board design
2018-12-27 Updated BLE connection for Wear OS client to connect to device MAC rather than scanning.
    Attempt to better locate the relay when the number of BLE devices present is high.
2019-02-24 Clean up schematic
2019-02-25 Add library customizations
2019-02-26 Begin esp32 board version
2019-02-26 Update to eagle version
2019-03-02 Consolidate libraries, swap regulator
2019-03-04 Removed unused parts for esp32, begin integrating actual module
2019-03-08 Board layout with UART but without LIPO charger, submitted this one to PCBA
2019-04-15 Add esp32 arduino project
2019-05-22 Software work for ESP32 version
2019-05-22 Add BOM for esp32 PCB
2019-05-22 Remove deprecated Ionic 1 app
2019-05-24 ESP32 single stick control via BLE
2019-05-24 Single-stick BLE control fully working, including fading.
2019-05-25 Get ready for mesh
2019-05-27 Add mesh init
2019-05-30 Mesh basically working with BLE and button
2019-06-07 Reorganized to accomodate platformio
2019-06-07 Add content for platformio
2019-06-08 BLE-Mesh relaying is reasonably reliable now.
2019-06-23 Mesh stability tests, but these don't work
2019-06-23 ESP-NOW broadcast now working, both BLE & switches No repeating/rebroadcasting yet.
2019-06-24 Use unions for protocol, drop CPU clock for power.
2019-06-26 Sequence number retransmit working.
2019-06-27 Change button behavior to be more like the X10-III instead of RGBCMY.
2019-06-28 Updated to work with a release build using proguard
2019-07-02 Minor power tuning
2019-10-24 Changed double-click, updated android project. vBatLED() can sometimes crash, plus is not accurate if measured while the light is on.
2019-11-15 Added rudimentary master-stick periodic resend.
2019-11-29 Update android libraries to newest
2019-11-29 Fix conflict
2019-12-15 CHange to BLE advertising
2019-12-25 Removed advanced advertisements that were confusing Wear OS

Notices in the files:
parts and their libraries:
SparkFun-Batteries: Licensing: Creative Commons ShareAlike 4.0 International - https://creativecommons.org/licenses/by-sa/4.0
